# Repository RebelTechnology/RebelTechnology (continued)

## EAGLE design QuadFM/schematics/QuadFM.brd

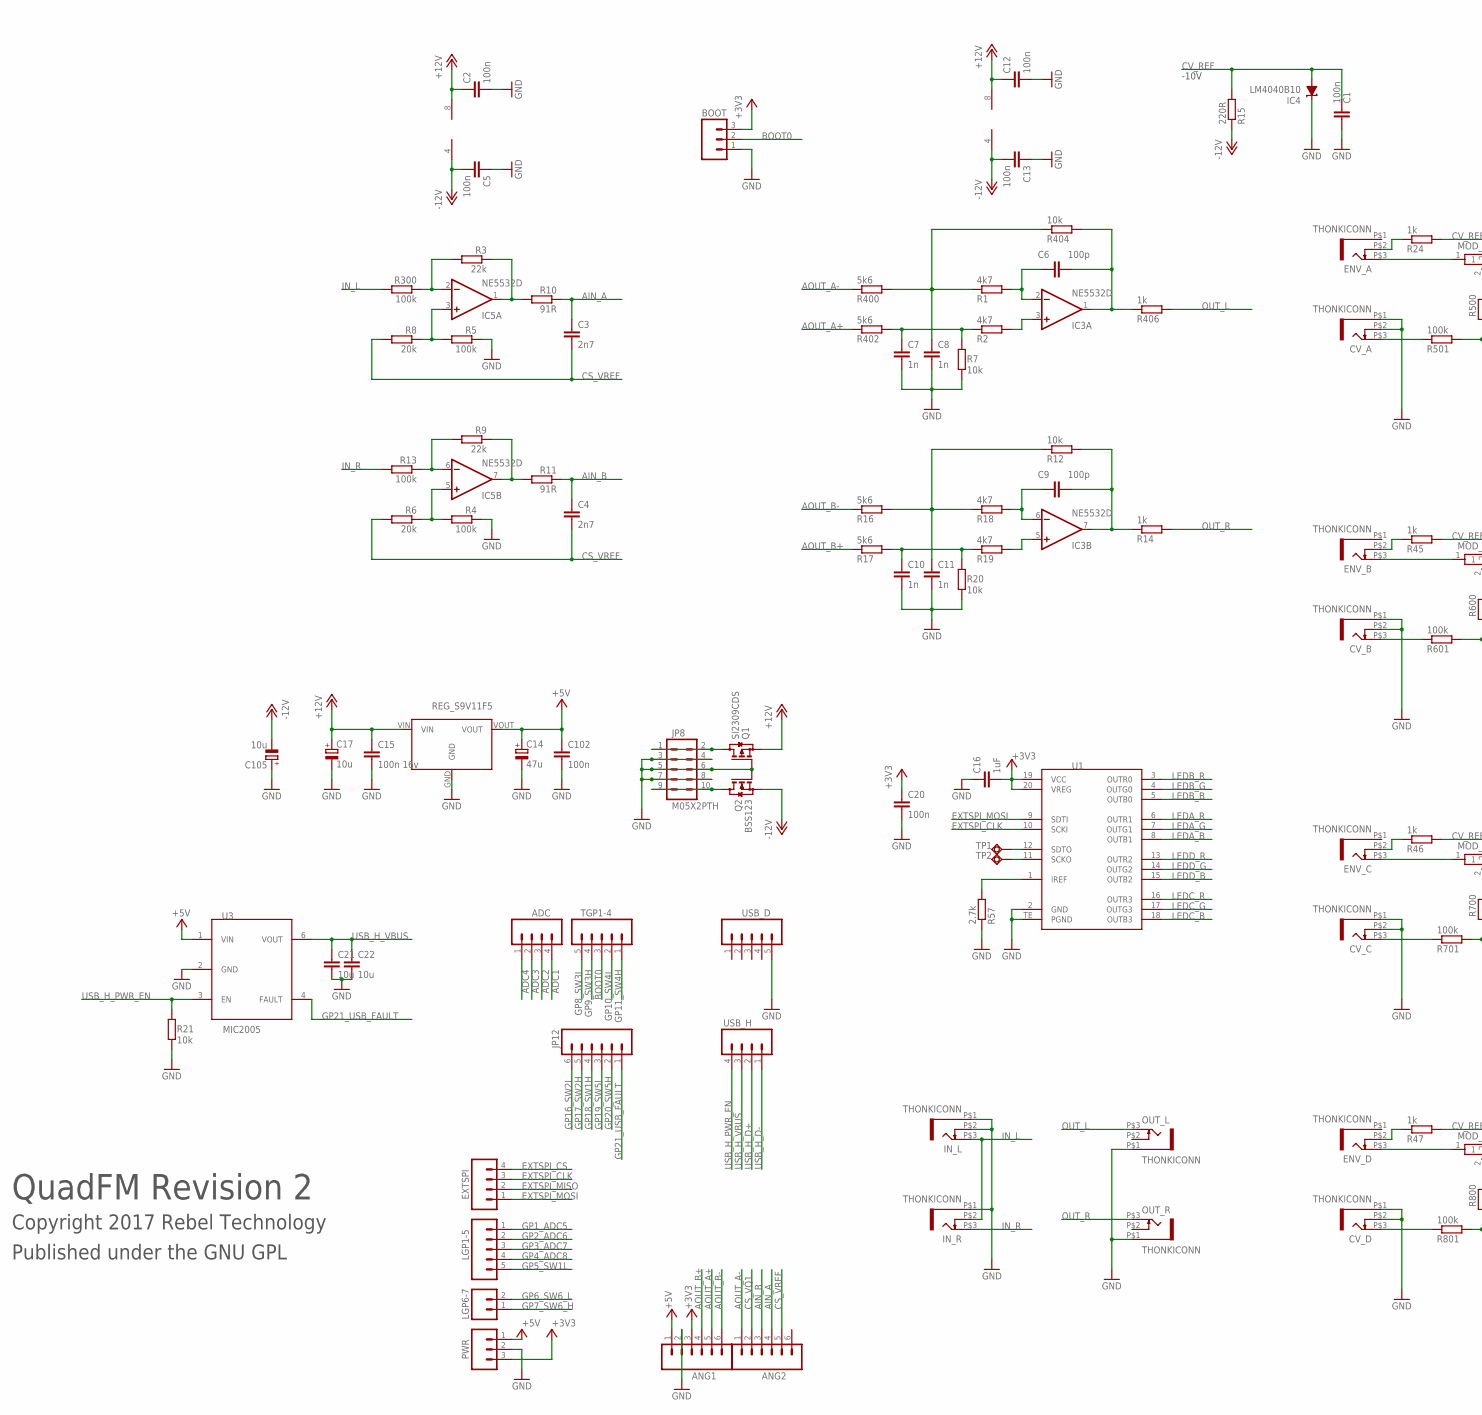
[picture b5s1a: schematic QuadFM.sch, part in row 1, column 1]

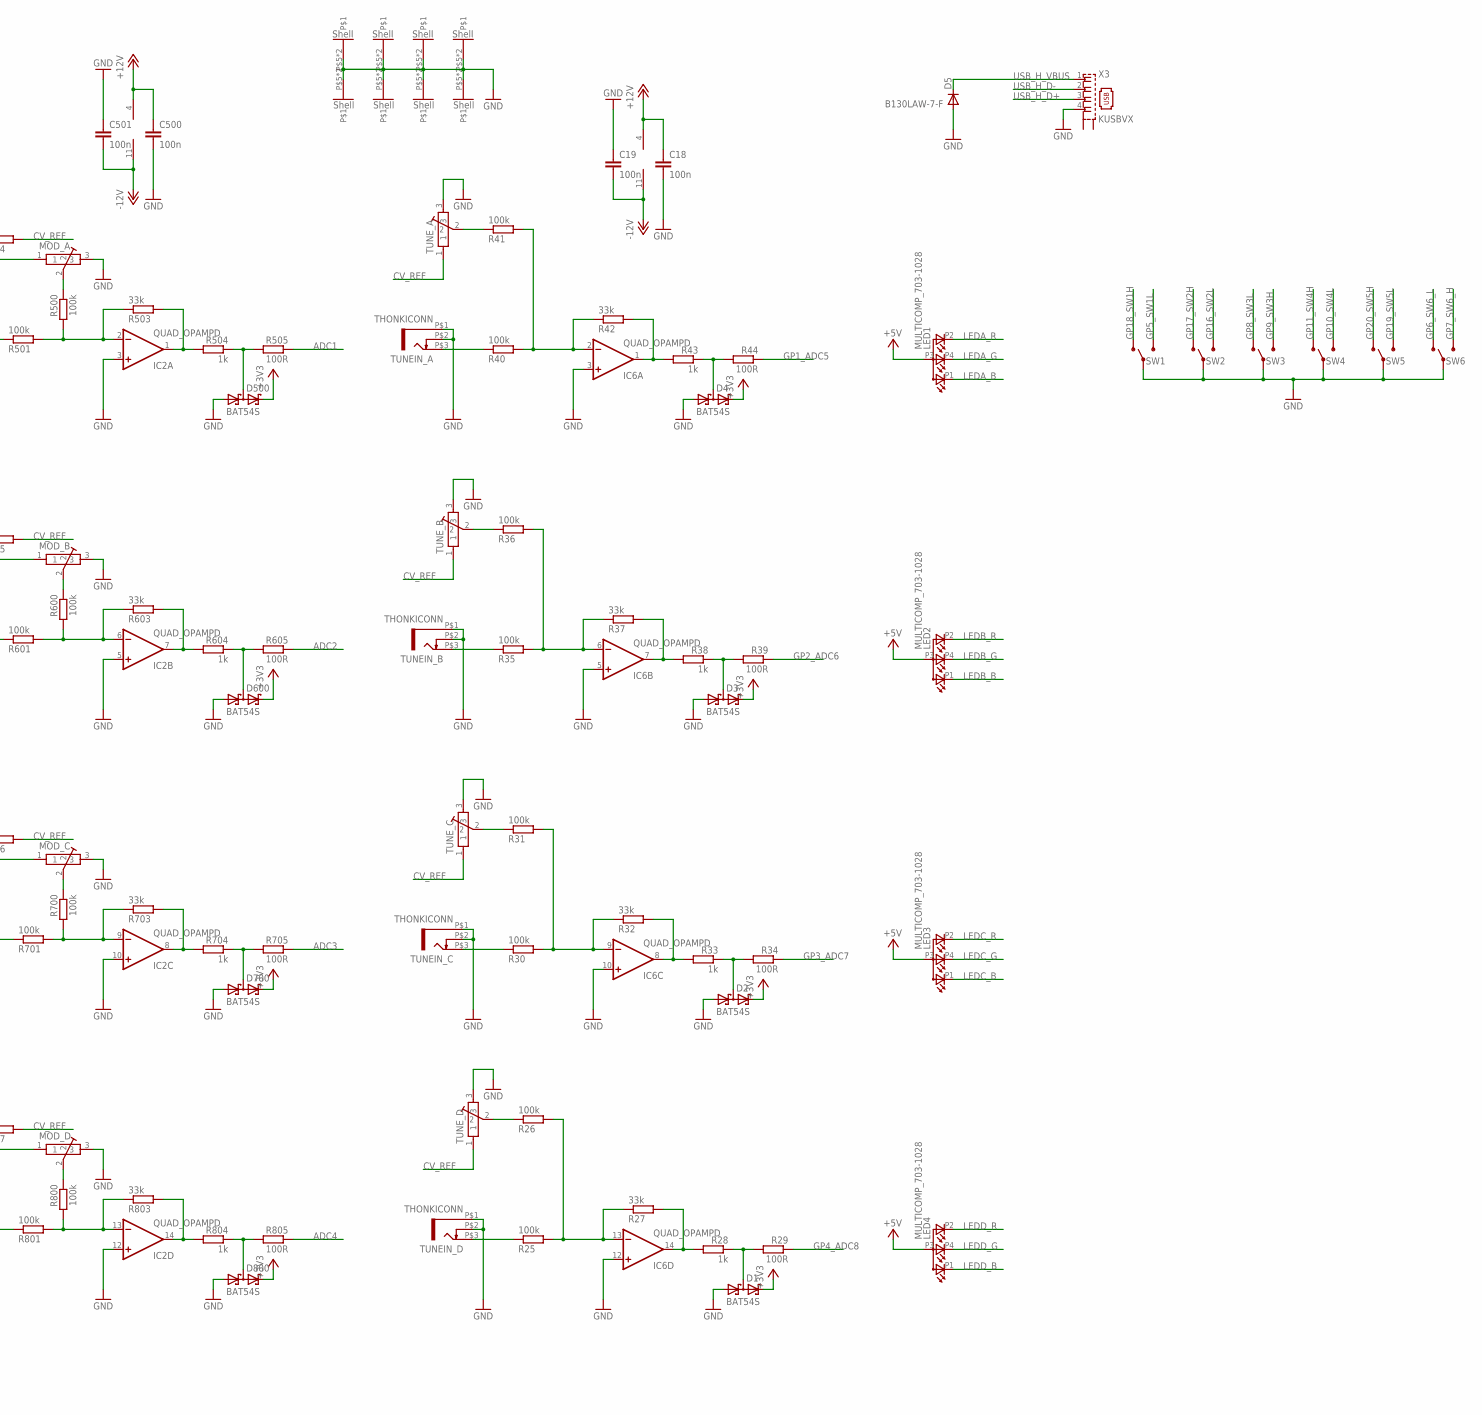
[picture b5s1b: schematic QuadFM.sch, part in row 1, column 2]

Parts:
ADC: M04PTH; 1X04
ANG1, ANG2: M06SIP; 1X06
BOOT: M03PTH; 1X03
C1, C2, C5, C12, C13, C18, C19, C20, C102, C500, C501: 100n; C0603
C3, C4: 2n7; C0603
C6, C9: 100p; C0603
C7, C8, C10, C11: 1n; C0603
C14: 47u; CPOL-5
C15: 100n 16v; C0603
C16: 1uF; C0603
C17, C105: 10u; 153CLV-0405
C21, C22: 10u; C0603
CV_A: THONKICONN
CV_B: THONKICONN
CV_C: THONKICONN
CV_D: THONKICONN
D1, D2, D3, D4, D500, D600, D700, D800: BAT54S; SOT23
D5: B130LAW-7-F; SOD123
ENV_A: THONKICONN
ENV_B: THONKICONN
ENV_C: THONKICONN
ENV_D: THONKICONN
EXTSPI: M04PTH; 1X04
IC2, IC6: QUAD_OPAMPD; SO14
IC3, IC5: NE5532D; SO08
IC4: LM4040B10; DBZ_R-PDSO-G3
IN_L: THONKICONN
IN_R: THONKICONN
JP8: M05X2PTH; AVR_ICSP
JP12: M06SIP; 1X06
LED1, LED2, LED3, LED4: MULTICOMP_703-1028; RGB-LED-703-1028
LGP1-5: M05PTH; 1X05
LGP6-7: M02PTH; 1X02
MOD_A: POT-ALPS-RK09L1140
MOD_B: POT-ALPS-RK09L1140
MOD_C: POT-ALPS-RK09L1140
MOD_D: POT-ALPS-RK09L1140
OUT_L: THONKICONN
OUT_R: THONKICONN
PWR: M03PTH; 1X03
Q1: SI2309CDS; SOT23
Q2: BSS123; SOT23
R1, R2, R18, R19: 4k7; 0603
R3, R9: 22k; 0603
R4, R5, R13, R25, R26, R30, R31, R35, R36, R40, R41, R300, R500, R501, R600, R601, R700, R701, R800, R801: 100k; 0603
R6, R8: 20k; 0603
R7, R12, R20, R21, R404: 10k; 0603
R10, R11: 91R; 0603
R14, R24, R28, R33, R38, R43, R45, R46, R47, R406, R504, R604, R704, R804: 1k; 0603
R15: 220R; 0603
R16, R17, R400, R402: 5k6; 0603
R27, R32, R37, R42, R503, R603, R703, R803: 33k; 0603
R29, R34, R39, R44, R505, R605, R705, R805: 100R; 0603
R57: 2.7k; 0603
SW1, SW2, SW3, SW4, SW5, SW6: SUB-MIN-SPDT
TGP1-4: M05PTH; 1X05
TP1, TP2: TPSQPAD1-13; P1-13
TUNEIN_A: THONKICONN
TUNEIN_B: THONKICONN
TUNEIN_C: THONKICONN
TUNEIN_D: THONKICONN
TUNE_A: POT-ALPS-RK09L1140
TUNE_B: POT-ALPS-RK09L1140
TUNE_C: POT-ALPS-RK09L1140
TUNE_D: POT-ALPS-RK09L1140
U1: TLC5971; TSSOP20-TE
U3: MIC2005; SOT23-6
U$1: REG_S9V11F5
USB_D: M05PTH; 1X05
USB_H: M04PTH; 1X04
X3: KUSBVX

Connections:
+3V3: ANG1.3, BOOT.3, C16.2, C20.1, D1.2 (C2), D2.2 (C2), D3.2 (C2), D4.2 (C2), D500.2 (C2), D600.2 (C2), D700.2 (C2), D800.2 (C2), PWR.3, U1.19 (VCC), U1.20 (VREG)
+5V: ANG1.1, C14.+, C102.1, LED1.P3 (A), LED2.P3 (A), LED3.P3 (A), LED4.P3 (A), PWR.1, U3.1 (VIN), U$1.VOUT
+12V: C2.1, C12.1, C15.1, C17.+, C18.1, C500.1, IC2.4 (V+), IC3.8 (V+), IC5.8 (V+), IC6.4 (V+), Q1.2 (S), U$1.VIN
-12V: C5.2, C13.2, C19.2, C105.-, C501.2, IC2.11 (V-), IC3.4 (V-), IC5.4 (V-), IC6.11 (V-), Q2.2 (S), R15.1
ADC1: ADC.4, R505.1
ADC2: ADC.3, R605.1
ADC3: ADC.2, R705.1
ADC4: ADC.1, R805.1
AIN_A: ANG2.4, C3.1, R10.1
AIN_B: ANG2.3, C4.1, R11.1
AOUT_A+: ANG1.5, R402.1
AOUT_A-: ANG2.1, R400.1
AOUT_B+: ANG1.4, R17.1
AOUT_B-: ANG1.6, R16.1
BOOT0: BOOT.2, TGP1-4.3
CS_VQ1: ANG2.2
CS_VREF: ANG2.5, C3.2, C4.2, R6.2, R8.2
CV_REF: C1.1, IC4.2 (A), R15.2, R24.2, R45.2, R46.2, R47.2, TUNE_A.1, TUNE_B.1, TUNE_C.1, TUNE_D.1
EXTSPI_CLK: EXTSPI.3, U1.10 (SCKI)
EXTSPI_CS: EXTSPI.4
EXTSPI_MISO: EXTSPI.2
EXTSPI_MOSI: EXTSPI.1, U1.9 (SDTI)
GND: ANG1.2, BOOT.1, C1.2, C2.2, C5.1, C7.2, C8.2, C10.2, C11.2, C12.2, C13.1, C14.-, C15.2, C16.1, C17.-, C18.2, C19.1, C20.2, C21.2, C22.2, C102.2, C105.+, C500.2, C501.1, CV_A.P$1 (5), CV_A.P$2 (4), CV_B.P$1 (5), CV_B.P$2 (4), CV_C.P$1 (5), CV_C.P$2 (4), CV_D.P$1 (5), CV_D.P$2 (4), D1.1 (A1), D2.1 (A1), D3.1 (A1), D4.1 (A1), D5.A, D500.1 (A1), D600.1 (A1), D700.1 (A1), D800.1 (A1), IC2.3 (+IN), IC2.5 (+IN), IC2.10 (+IN), IC2.12 (+IN), IC4.1 (C), IC6.3 (+IN), IC6.5 (+IN), IC6.10 (+IN), IC6.12 (+IN), IN_L.P$1 (5), IN_L.P$2 (4), IN_R.P$1 (5), JP8.3, JP8.4, JP8.5, JP8.6, JP8.7, JP8.8, MOD_A.3, MOD_A.P$5, MOD_A.P$6, MOD_B.3, MOD_B.P$5, MOD_B.P$6, MOD_C.3, MOD_C.P$5, MOD_C.P$6, MOD_D.3, MOD_D.P$5, MOD_D.P$6, OUT_L.P$1 (5), OUT_R.P$1 (5), PWR.2, Q1.1 (G), Q2.1 (G), R4.1, R5.1, R7.1, R20.1, R21.1, R57.1, SW1.2, SW2.2, SW3.2, SW4.2, SW5.2, SW6.2, TUNEIN_A.P$1 (5), TUNEIN_A.P$2 (4), TUNEIN_B.P$1 (5), TUNEIN_B.P$2 (4), TUNEIN_C.P$1 (5), TUNEIN_C.P$2 (4), TUNEIN_D.P$1 (5), TUNEIN_D.P$2 (4), TUNE_A.3, TUNE_A.P$5, TUNE_A.P$6, TUNE_B.3, TUNE_B.P$5, TUNE_B.P$6, TUNE_C.3, TUNE_C.P$5, TUNE_C.P$6, TUNE_D.3, TUNE_D.P$5, TUNE_D.P$6, U1.2 (GND), U1.TE (PGND), U3.2 (GND), U$1.GND, USB_D.5, X3.4
GP1_ADC5: LGP1-5.1, R44.1
GP2_ADC6: LGP1-5.2, R39.1
GP3_ADC7: LGP1-5.3, R34.1
GP4_ADC8: LGP1-5.4, R29.1
GP5_SW1L: LGP1-5.5, SW1.3 (S)
GP6_SW6_L: LGP6-7.2, SW6.1 (O)
GP7_SW6_H: LGP6-7.1, SW6.3 (S)
GP8_SW3L: SW3.1 (O), TGP1-4.5
GP9_SW3H: SW3.3 (S), TGP1-4.4
GP10_SW4L: SW4.3 (S), TGP1-4.2
GP11_SW4H: SW4.1 (O), TGP1-4.1
GP16_SW2L: JP12.6, SW2.3 (S)
GP17_SW2H: JP12.5, SW2.1 (O)
GP18_SW1H: JP12.4, SW1.1 (O)
GP19_SW5L: JP12.3, SW5.3 (S)
GP20_SW5H: JP12.2, SW5.1 (O)
GP21_USB_FAULT: JP12.1, U3.4 (FAULT)
IN_L: IN_L.P$3 (3), IN_R.P$2 (4), R300.2
IN_R: IN_R.P$3 (3), R13.2
LEDA_B: LED1.P1 (CRED), U1.8 (OUTB1)
LEDA_G: LED1.P4 (CBLUE), U1.7 (OUTG1)
LEDA_R: LED1.P2 (CGREEN), U1.6 (OUTR1)
LEDB_B: LED2.P1 (CRED), U1.5 (OUTB0)
LEDB_G: LED2.P4 (CBLUE), U1.4 (OUTG0)
LEDB_R: LED2.P2 (CGREEN), U1.3 (OUTR0)
LEDC_B: LED3.P1 (CRED), U1.18 (OUTB3)
LEDC_G: LED3.P4 (CBLUE), U1.17 (OUTG3)
LEDC_R: LED3.P2 (CGREEN), U1.16 (OUTR3)
LEDD_B: LED4.P1 (CRED), U1.15 (OUTB2)
LEDD_G: LED4.P4 (CBLUE), U1.14 (OUTG2)
LEDD_R: LED4.P2 (CGREEN), U1.13 (OUTR2)
unnamed: IC5.1 (OUT), R3.1, R10.2
unnamed: IC5.3 (+IN), R5.2, R8.1
unnamed: CV_A.P$3 (3), R501.1
unnamed: IC5.5 (+IN), R4.2, R6.1
unnamed: IC5.6 (-IN), R9.2, R13.1
unnamed: IC2.9 (-IN), R700.2, R701.2, R703.1
unnamed: C6.1, IC3.2 (-IN), R1.2
unnamed: JP8.9, JP8.10, Q2.3 (D)
unnamed: IC5.2 (-IN), R3.2, R300.1
unnamed: IC5.7 (OUT), R9.1, R11.2
unnamed: IC3.3 (+IN), R2.2
unnamed: JP8.1, JP8.2, Q1.3 (D)
unnamed: IC2.2 (-IN), R500.2, R501.2, R503.1
unnamed: MOD_A.2, R500.1
unnamed: C7.1, R2.1, R7.2, R402.2
unnamed: D500.3 (C1A2), R504.1, R505.2
unnamed: IC2.1 (OUT), R503.2, R504.2
unnamed: C9.2, IC3.7 (OUT), R12.2, R14.1
unnamed: CV_B.P$3 (3), R601.1
unnamed: IC2.6 (-IN), R600.2, R601.2, R603.1
unnamed: MOD_B.2, R600.1
unnamed: IC2.7 (OUT), R603.2, R604.2
unnamed: D600.3 (C1A2), R604.1, R605.2
unnamed: C11.1, R12.1, R16.2, R18.1
unnamed: CV_C.P$3 (3), R701.1
unnamed: C9.1, IC3.6 (-IN), R18.2
unnamed: MOD_C.2, R700.1
unnamed: IC2.8 (OUT), R703.2, R704.2
unnamed: D700.3 (C1A2), R704.1, R705.2
unnamed: IC3.5 (+IN), R19.2
unnamed: CV_D.P$3 (3), R801.1
unnamed: C10.1, R17.2, R19.1, R20.2
unnamed: IC2.13 (-IN), R800.2, R801.2, R803.1
unnamed: MOD_D.2, R800.1
unnamed: IC2.14 (OUT), R803.2, R804.2
unnamed: D800.3 (C1A2), R804.1, R805.2
unnamed: ENV_A.P$2 (4), R24.1
unnamed: C6.2, IC3.1 (OUT), R404.2, R406.1
unnamed: TP1.TP, U1.12 (SDTO)
unnamed: C8.1, R1.1, R400.2, R404.1
unnamed: TP2.TP, U1.11 (SCKO)
unnamed: ENV_A.P$3 (3), MOD_A.1
unnamed: R25.1, TUNEIN_D.P$3 (3)
unnamed: R57.2, U1.1 (IREF)
unnamed: IC6.13 (-IN), R25.2, R26.2, R27.1
unnamed: R26.1, TUNE_D.2
unnamed: IC6.14 (OUT), R27.2, R28.2
unnamed: D1.3 (C1A2), R28.1, R29.2
unnamed: R30.1, TUNEIN_C.P$3 (3)
unnamed: IC6.9 (-IN), R30.2, R31.2, R32.1
unnamed: R31.1, TUNE_C.2
unnamed: IC6.8 (OUT), R32.2, R33.2
unnamed: D2.3 (C1A2), R33.1, R34.2
unnamed: R35.1, TUNEIN_B.P$3 (3)
unnamed: IC6.6 (-IN), R35.2, R36.2, R37.1
unnamed: R36.1, TUNE_B.2
unnamed: IC6.7 (OUT), R37.2, R38.2
unnamed: D3.3 (C1A2), R38.1, R39.2
unnamed: R40.1, TUNEIN_A.P$3 (3)
unnamed: IC6.2 (-IN), R40.2, R41.2, R42.1
unnamed: R41.1, TUNE_A.2
unnamed: IC6.1 (OUT), R42.2, R43.2
unnamed: D4.3 (C1A2), R43.1, R44.2
unnamed: ENV_B.P$2 (4), R45.1
unnamed: ENV_B.P$3 (3), MOD_B.1
unnamed: ENV_C.P$2 (4), R46.1
unnamed: ENV_C.P$3 (3), MOD_C.1
unnamed: ENV_D.P$2 (4), R47.1
unnamed: ENV_D.P$3 (3), MOD_D.1
OUT_L: OUT_L.P$3 (3), R406.2
OUT_R: OUT_R.P$3 (3), R14.2
USB_H_D+: USB_H.2, X3.3
USB_H_D-: USB_H.1, X3.2
USB_H_PWR_EN: R21.2, U3.3 (EN), USB_H.4
USB_H_VBUS: C21.1, C22.1, D5.C, U3.6 (VOUT), USB_H.3, X3.1

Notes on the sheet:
QuadFM Revision 2
Copyright 2017 Rebel Technology
Published under the GNU GPL
-10V

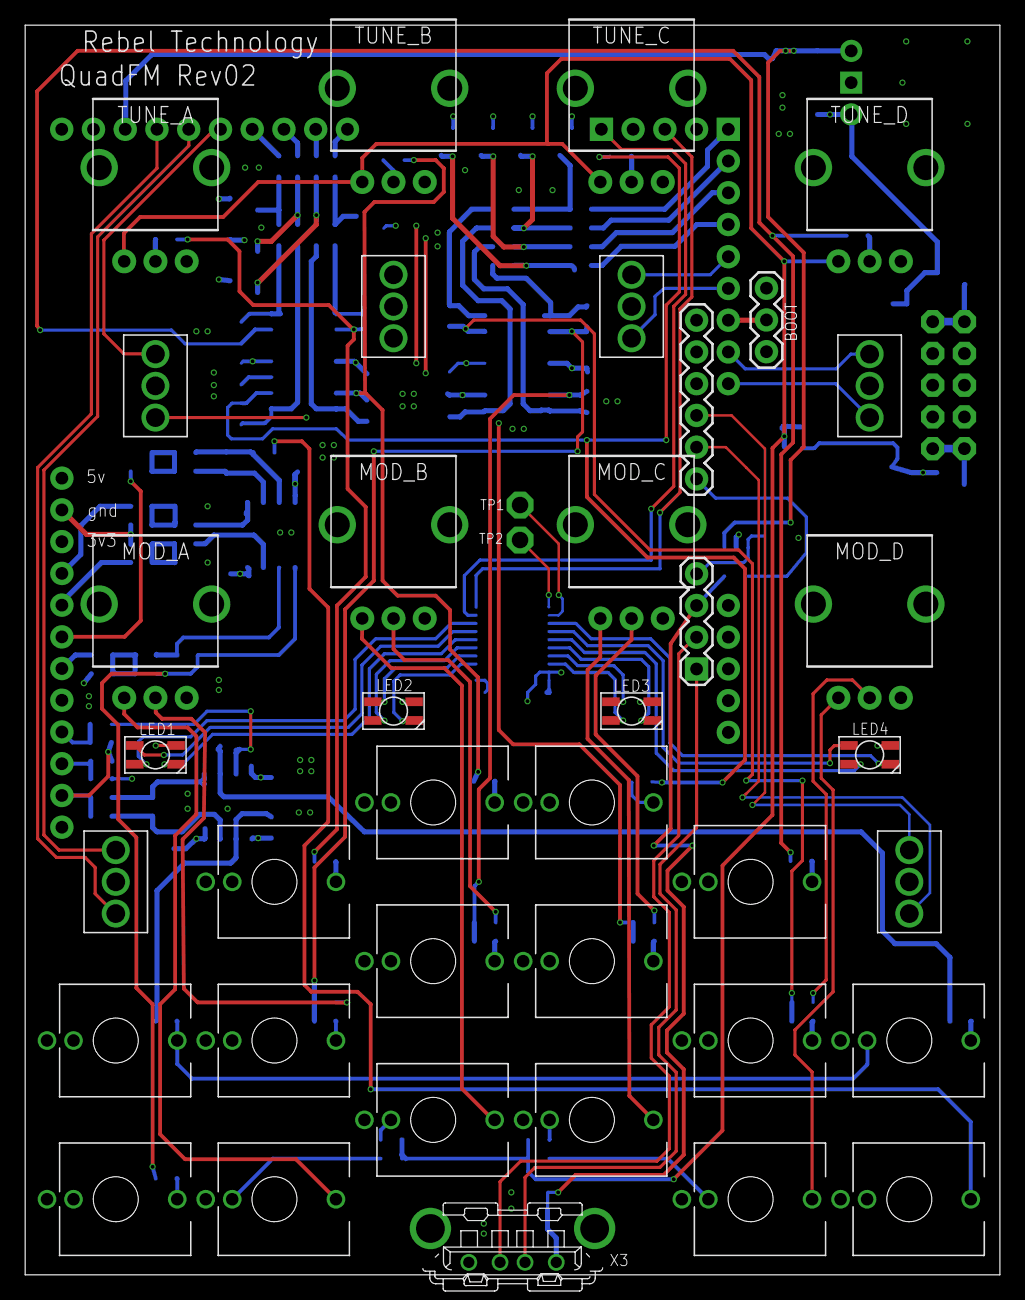
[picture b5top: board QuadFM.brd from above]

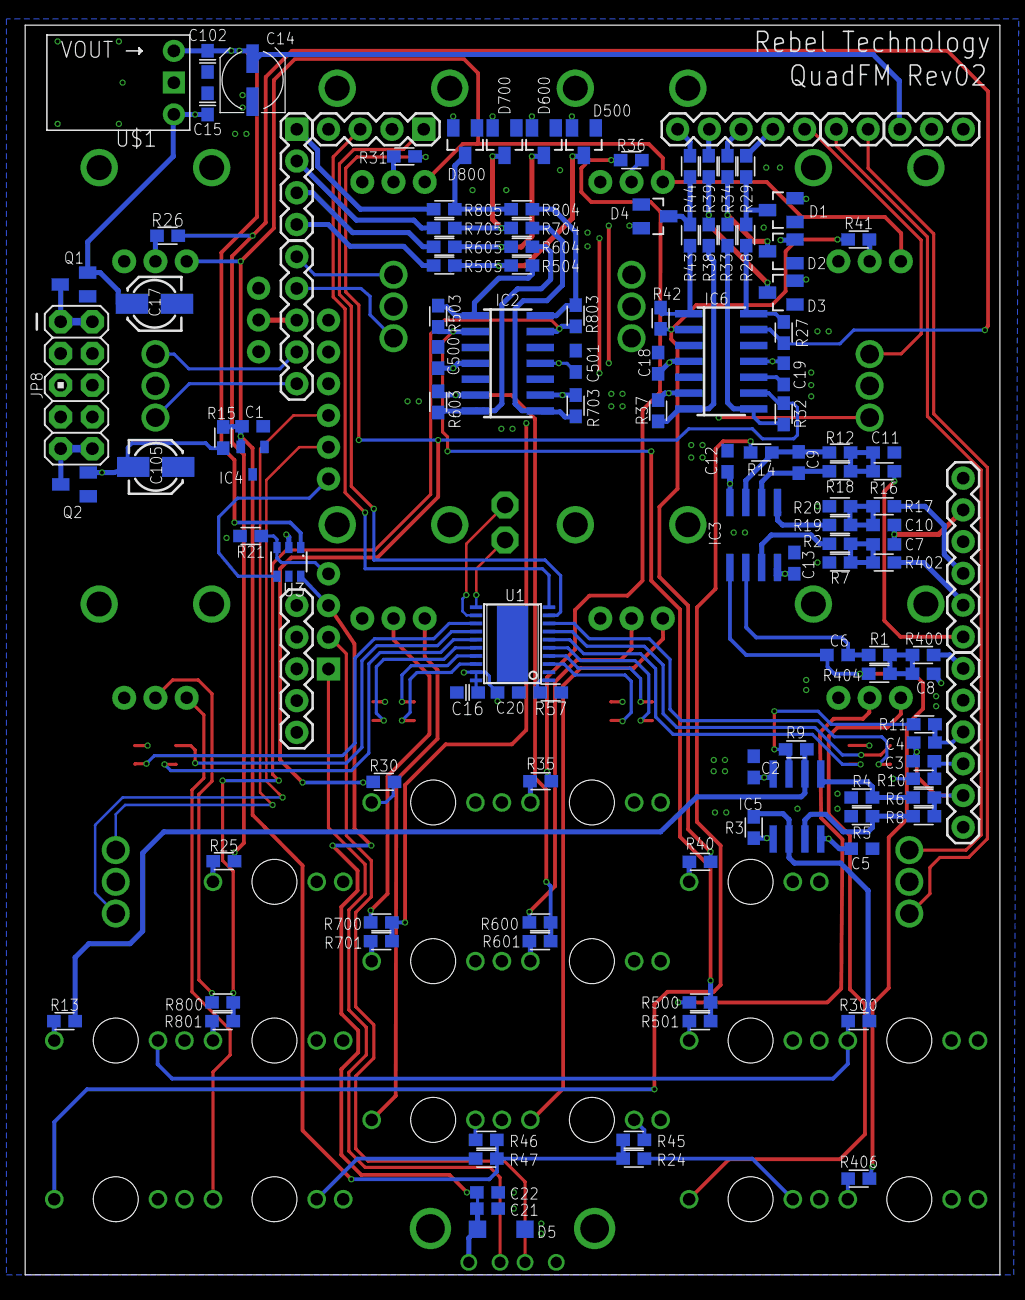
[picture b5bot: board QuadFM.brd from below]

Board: 4 copper layers, 78.0 x 100.0 mm, 166 parts (126 on the bottom side), 126 nets.

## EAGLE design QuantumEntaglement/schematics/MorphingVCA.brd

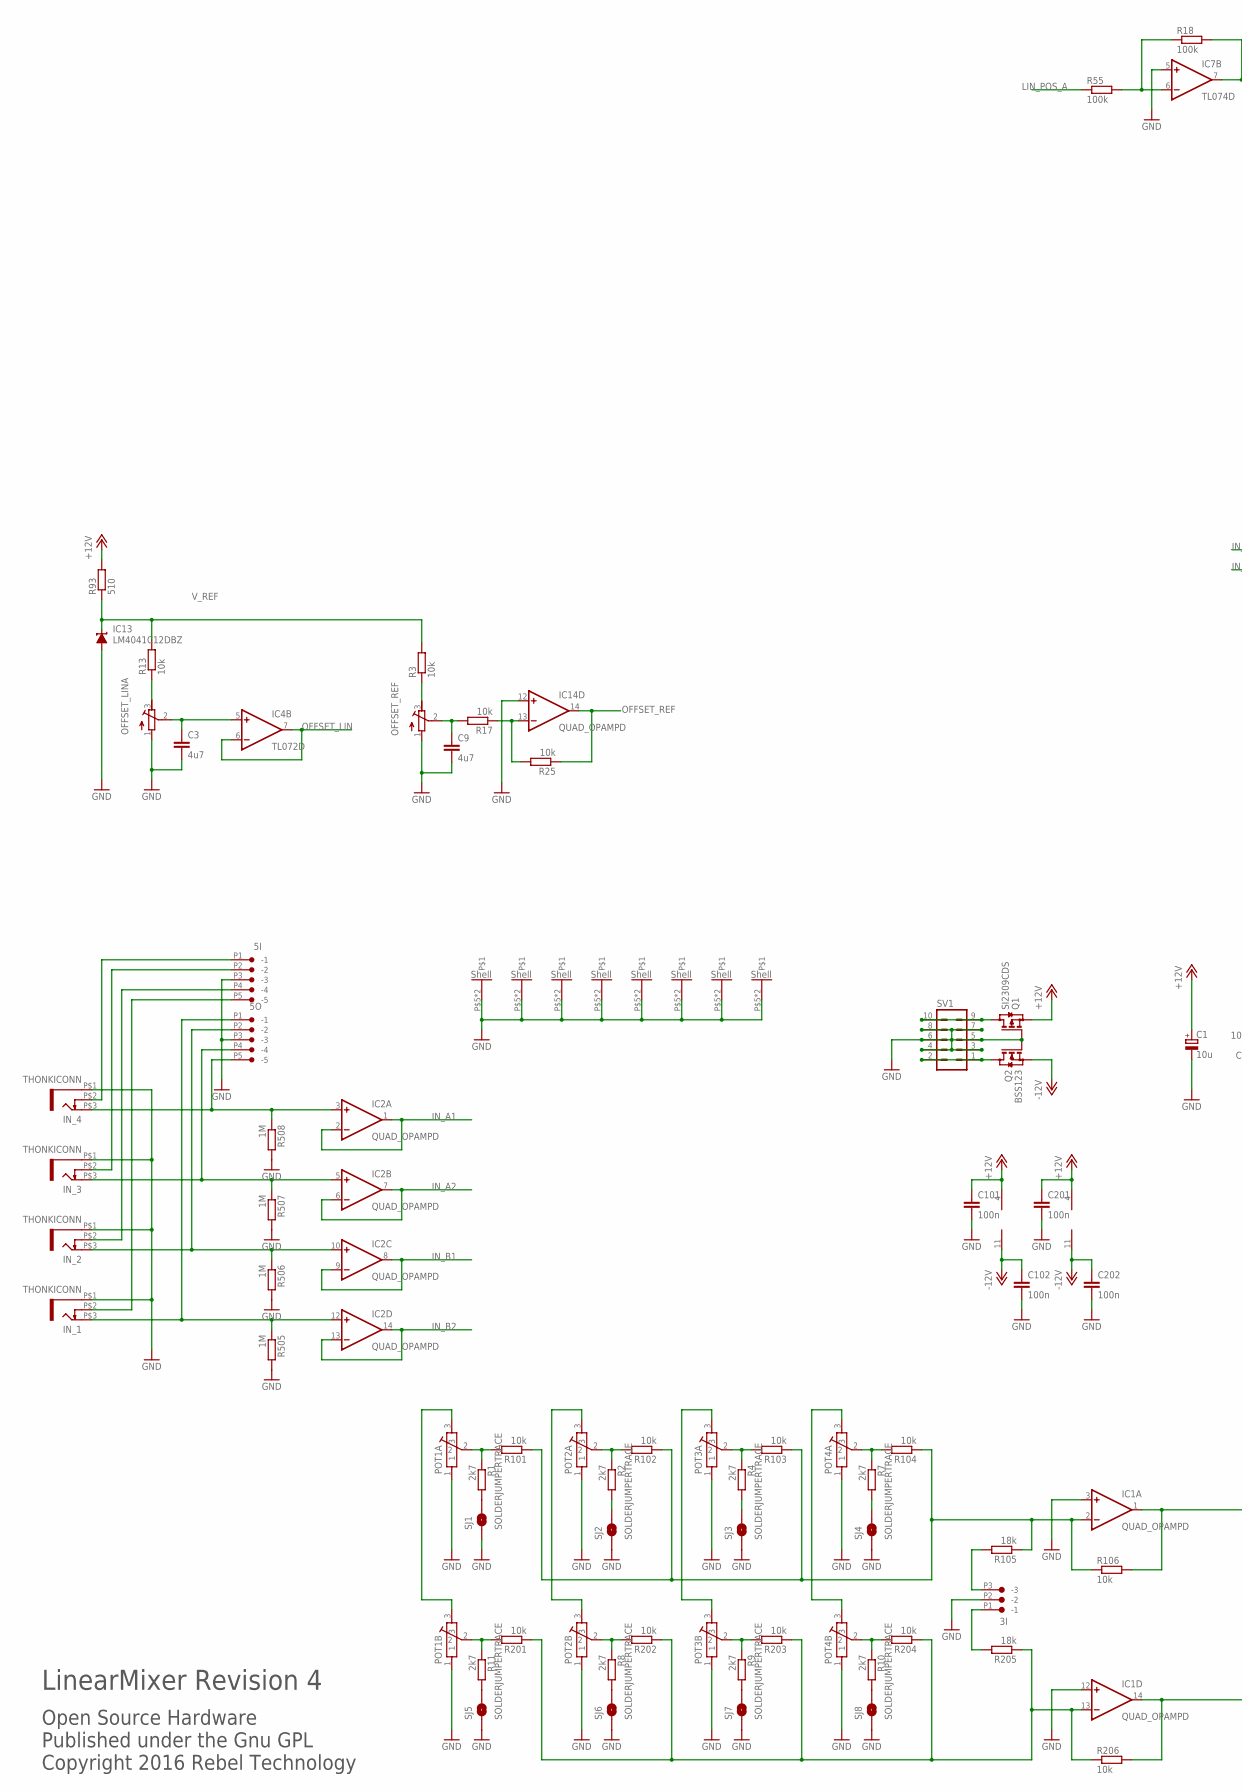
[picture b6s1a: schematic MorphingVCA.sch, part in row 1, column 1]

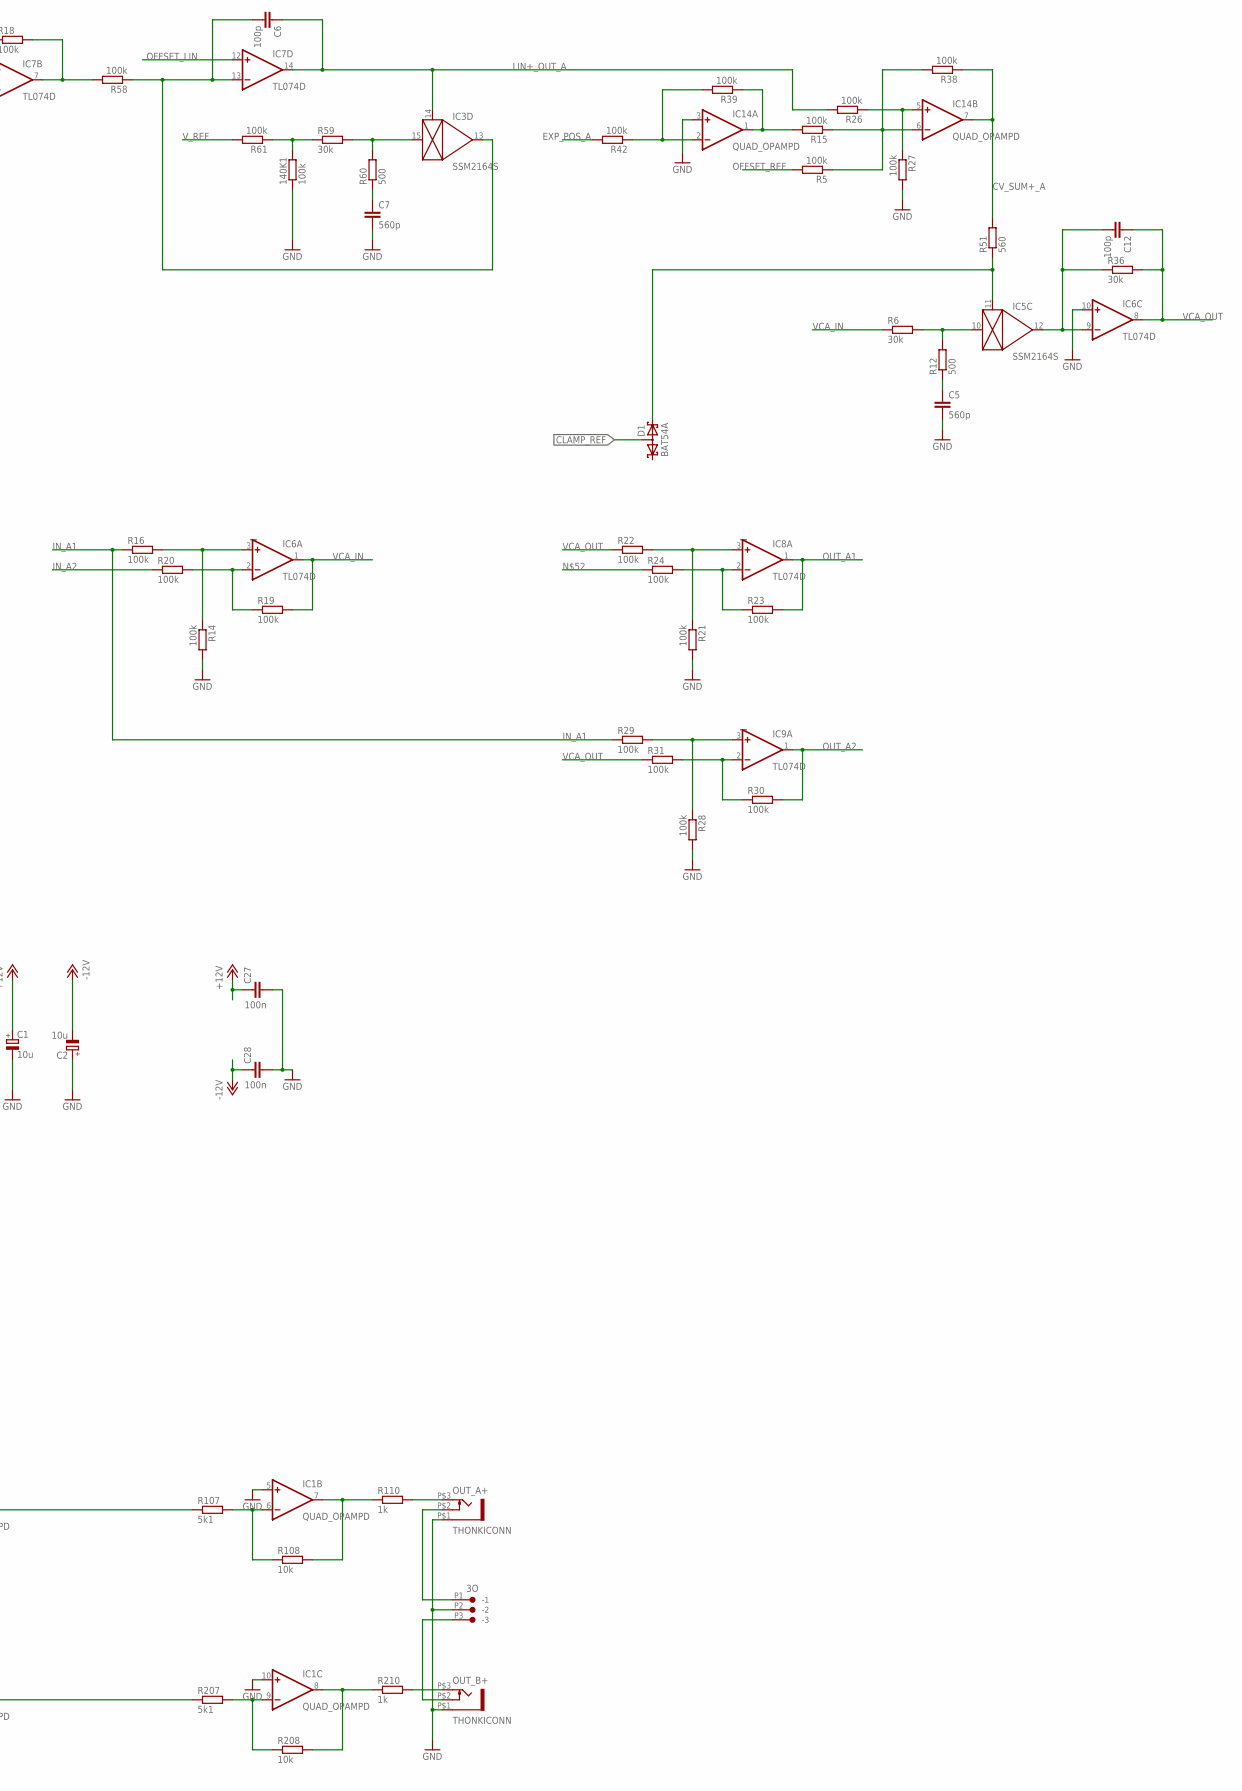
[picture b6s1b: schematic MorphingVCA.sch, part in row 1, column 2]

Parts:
3I, 3O: CON-JST_PH_3W
5I, 5O: CON-JST_PH_5W
140K1: 100k; 0603
C1, C2: 10u; 153CLV-0505
C3, C9: 4u7; C0603K
C5, C7: 560p; C0603K
C6, C12: 100p; C0603K
C27, C28, C101, C102, C201, C202: 100n; C0603
D1: BAT54A; SOT23
IC1, IC2, IC14: QUAD_OPAMPD; SO14
IC3, IC5: SSM2164S; SOIC16N
IC4: TL072D; SO08
IC6, IC7, IC8, IC9: TL074D; SO14
IC13: LM4041C12DBZ; DBZ_R-PDSO-G3
IN_1, IN_2, IN_3, IN_4: THONKICONN
OFFSET_LINA: R-TRIMM64W; RTRIM64W
OFFSET_REF: R-TRIMM64W; RTRIM64W
OUT_A+: THONKICONN
OUT_B+: THONKICONN
POT1A, POT1B, POT2A, POT2B, POT3A, POT3B, POT4A, POT4B: POT-ALPS-RK09L1140
Q1: SI2309CDS; SOT23
Q2: BSS123; SOT23
R1, R2, R4, R7, R8, R9, R10, R11: 2k7; R0603
R3, R13, R17, R25: 10k; 0603
R5, R14, R15, R16, R18, R19, R20, R21, R22, R23, R24, R26, R27, R28, R29, R30, R31, R38, R39, R42, R55, R58, R61: 100k; 0603
R6, R36, R59: 30k; 0603
R12, R60: 500; 0603
R51: 560; 0603
R93: 510; 0603
R101, R102, R103, R104, R106, R108, R201, R202, R203, R204, R206, R208: 10k; R0603
R105, R205: 18k; R0603
R107, R207: 5k1; R0603
R110, R210: 1k; R0603
R505, R506, R507, R508: 1M; R0603
SJ1, SJ2, SJ3, SJ4, SJ5, SJ6, SJ7, SJ8: SOLDERJUMPERTRACE; SJ_2S-TRACE
SV1: MA05-2

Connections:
+12V: C1.+, C27.1, C101.1, C201.1, IC1.4 (V+), IC2.4 (V+), Q1.2 (S), R93.2
-10V1: 140K1.2, R59.1, R61.1
-12V: C2.-, C28.1, C102.1, C202.1, IC1.11 (V-), IC2.11 (V-), Q2.2 (S)
CLAMP_REF: D1.3 (AA)
CV_SUM+_A: IC14.7 (OUT), R38.1, R51.2
EXP_POS_A: R42.2
GND: 3I.P2 (-2), 3O.P2 (-2), 5I.P3 (-3), 5O.P3 (-3), 140K1.1, C1.-, C2.+, C3.2, C5.2, C7.2, C9.2, C27.2, C28.2, C101.2, C102.2, C201.2, C202.2, IC1.3 (+IN), IC1.5 (+IN), IC1.10 (+IN), IC1.12 (+IN), IC3.8 (GND), IC5.8 (GND), IC6.10 (+IN), IC7.5 (+IN), IC13.2 (A), IC14.3 (+IN), IC14.12 (+IN), IN_1.P$1 (5), IN_2.P$1 (5), IN_3.P$1 (5), IN_4.P$1 (5), OFFSET_LINA.1 (A), OFFSET_REF.1 (A), OUT_A+.P$1 (5), OUT_B+.P$1 (5), POT1A.1, POT1A.P$5, POT1A.P$6, POT1B.1, POT1B.P$5, POT1B.P$6, POT2A.1, POT2A.P$5, POT2A.P$6, POT2B.1, POT2B.P$5, POT2B.P$6, POT3A.1, POT3A.P$5, POT3A.P$6, POT3B.1, POT3B.P$5, POT3B.P$6, POT4A.1, POT4A.P$5, POT4A.P$6, POT4B.1, POT4B.P$5, POT4B.P$6, Q1.1 (G), Q2.1 (G), R14.2, R21.2, R27.2, R28.2, R505.2, R506.2, R507.2, R508.2, SJ1.1, SJ2.1, SJ3.1, SJ4.1, SJ5.1, SJ6.1, SJ7.1, SJ8.1, SV1.3, SV1.4, SV1.5, SV1.6, SV1.7, SV1.8
IC2C_11: D1.2 (K2), IC5.11 (CTRL), R51.1
IC2_8: IC14.6 (-IN), R5.1, R15.1, R38.2
IC2_13: C6.2, IC3.13 (OUT), IC7.13 (-IN), R58.1
IN_1: 5O.P1 (-1), IC2.12 (+IN), IN_1.P$3 (3), R505.1
IN_2: 5O.P2 (-2), IC2.10 (+IN), IN_2.P$3 (3), R506.1
IN_3: 5O.P4 (-4), IC2.5 (+IN), IN_3.P$3 (3), R507.1
IN_4: 5O.P5 (-5), IC2.3 (+IN), IN_4.P$3 (3), R508.1
IN_A: 3I.P3 (-3), R105.2
IN_A1: IC2.1 (OUT), IC2.2 (-IN), R16.1, R29.1
IN_A2: IC2.6 (-IN), IC2.7 (OUT), R20.1
IN_B: 3I.P1 (-1), R205.2
IN_B1: IC2.8 (OUT), IC2.9 (-IN)
IN_B2: IC2.13 (-IN), IC2.14 (OUT)
IN_SW_1: 5I.P5 (-5), IN_1.P$2 (4)
IN_SW_2: 5I.P4 (-4), IN_2.P$2 (4)
IN_SW_3: 5I.P2 (-2), IN_3.P$2 (4)
IN_SW_4: 5I.P1 (-1), IN_4.P$2 (4)
LIN+_OUT_A: C6.1, IC3.14 (CTRL), IC7.14 (OUT), R26.2
LIN_POS_A: R55.1
unnamed: Q2.3 (D), SV1.1, SV1.2
unnamed: IC7.7 (OUT), R18.2, R58.2
unnamed: IC7.6 (-IN), R18.1, R55.2
unnamed: OFFSET_LINA.3 (E), R13.1
unnamed: IC1.8 (OUT), R208.2, R210.1
unnamed: IC1.7 (OUT), R108.2, R110.1
unnamed: IC1.13 (-IN), R201.1, R202.1, R203.1, R204.1, R205.1, R206.1
unnamed: C3.1, IC4.5 (+IN), OFFSET_LINA.2 (S)
unnamed: OUT_A+.P$3 (3), R110.2
unnamed: IC1.14 (OUT), R206.2, R207.1
unnamed: IC1.2 (-IN), R101.1, R102.1, R103.1, R104.1, R105.1, R106.1
unnamed: IC14.2 (-IN), R39.2, R42.1
unnamed: IC1.1 (OUT), R106.2, R107.1
unnamed: Q1.3 (D), SV1.9, SV1.10
unnamed: OUT_B+.P$3 (3), R210.2
unnamed: IC14.1 (OUT), R15.2, R39.1
unnamed: R1.2, SJ1.2
unnamed: IC1.6 (-IN), R107.2, R108.1
unnamed: OFFSET_REF.3 (E), R3.1
unnamed: POT1B.2, R11.1, R201.2
unnamed: IC14.13 (-IN), R17.1, R25.2
unnamed: R2.2, SJ2.2
unnamed: IC1.9 (-IN), R207.2, R208.1
unnamed: R4.2, SJ3.2
unnamed: R7.2, SJ4.2
unnamed: R11.2, SJ5.2
unnamed: IC8.2 (-IN), R23.1, R24.2
unnamed: R8.2, SJ6.2
unnamed: POT1A.2, R1.1, R101.2
unnamed: POT2B.2, R8.1, R202.2
unnamed: POT3B.2, R9.1, R203.2
unnamed: R9.2, SJ7.2
unnamed: R10.2, SJ8.2
unnamed: POT1A.3, POT1B.3
unnamed: IC8.3 (+IN), R21.1, R22.2
unnamed: POT2A.3, POT2B.3
unnamed: POT3A.3, POT3B.3
unnamed: POT4A.3, POT4B.3
unnamed: IC14.5 (+IN), R26.1, R27.1
unnamed: C9.1, OFFSET_REF.2 (S), R17.2
unnamed: C5.1, R12.1
unnamed: IC5.10 (IN), R6.2, R12.2
unnamed: C12.2, IC5.12 (OUT), IC6.9 (-IN), R36.1
unnamed: POT4B.2, R10.1, R204.2
unnamed: IC9.2 (-IN), R30.1, R31.2
unnamed: IC6.2 (-IN), R19.1, R20.2
unnamed: POT4A.2, R7.1, R104.2
unnamed: IC6.3 (+IN), R14.1, R16.2
unnamed: POT3A.2, R4.1, R103.2
unnamed: POT2A.2, R2.1, R102.2
unnamed: IC9.3 (+IN), R28.1, R29.2
unnamed: C7.1, R60.1
unnamed: IC3.15 (IN), R59.2, R60.2
OFFSET_LIN: IC4.6 (-IN), IC4.7 (OUT), IC7.12 (+IN)
OFFSET_REF: IC14.14 (OUT), R5.2, R25.1
OUT_A1: IC8.1 (OUT), R23.2
OUT_A2: IC9.1 (OUT), R30.2
OUT_SW_A: 3O.P1 (-1), OUT_A+.P$2 (4)
OUT_SW_B: 3O.P3 (-3), OUT_B+.P$2 (4)
V+: IC3.16 (V+), IC4.8 (V+), IC5.16 (V+), IC6.4 (V+), IC7.4 (V+), IC8.4 (V+), IC9.4 (V+), IC14.4 (V+)
V-: IC3.9 (V-), IC4.4 (V-), IC5.9 (V-), IC6.11 (V-), IC7.11 (V-), IC8.11 (V-), IC9.11 (V-), IC14.11 (V-)
VCA_IN: IC6.1 (OUT), R6.1, R19.2
VCA_OUT: C12.1, IC6.8 (OUT), R22.1, R31.1, R36.2
V_REF: IC13.1 (C), R3.2, R13.2, R61.2, R93.1

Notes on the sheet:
Open Source Hardware Published under the Gnu GPL Copyright 2016 Rebel Technology
LinearMixer Revision 4

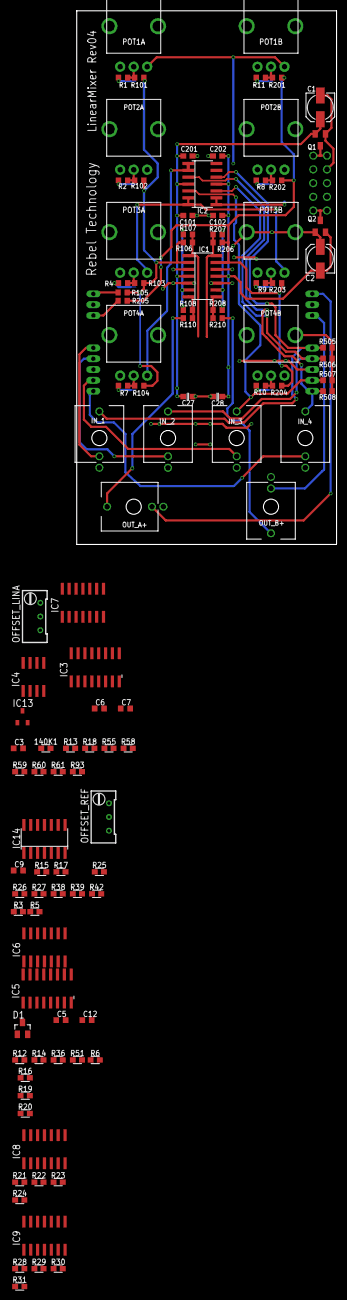
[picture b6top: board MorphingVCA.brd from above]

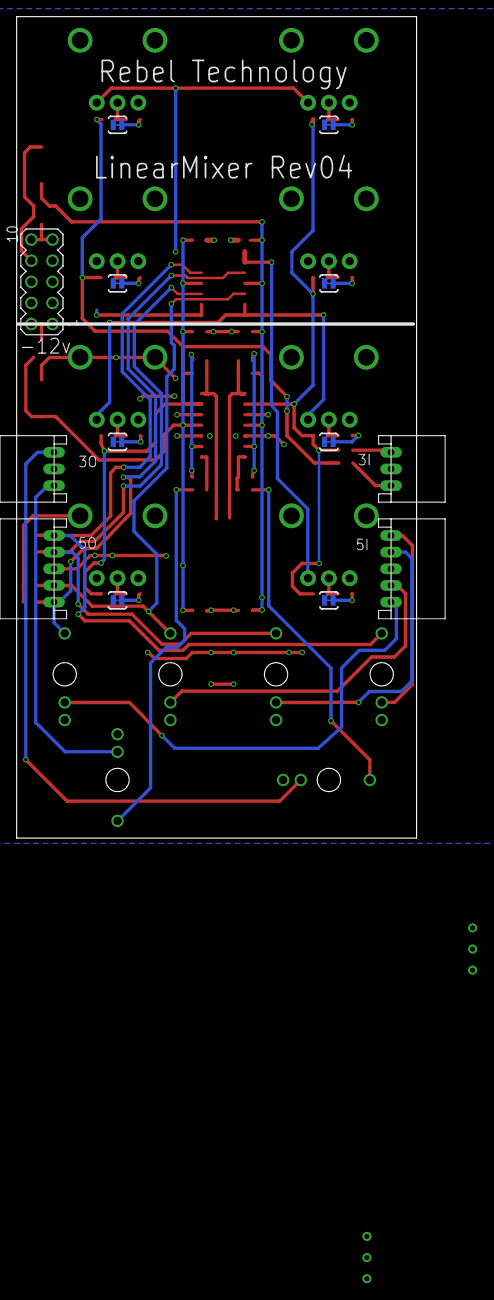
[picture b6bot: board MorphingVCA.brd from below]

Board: 2 copper layers, 48.1 x 98.7 mm, 122 parts (13 on the bottom side), 87 nets.
